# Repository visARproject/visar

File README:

Right now this is just an example of a simple OpenGL program

FIRST

  $ git submodule update --init

BUILDING

  $ scons

RUNNING

  $ build/main

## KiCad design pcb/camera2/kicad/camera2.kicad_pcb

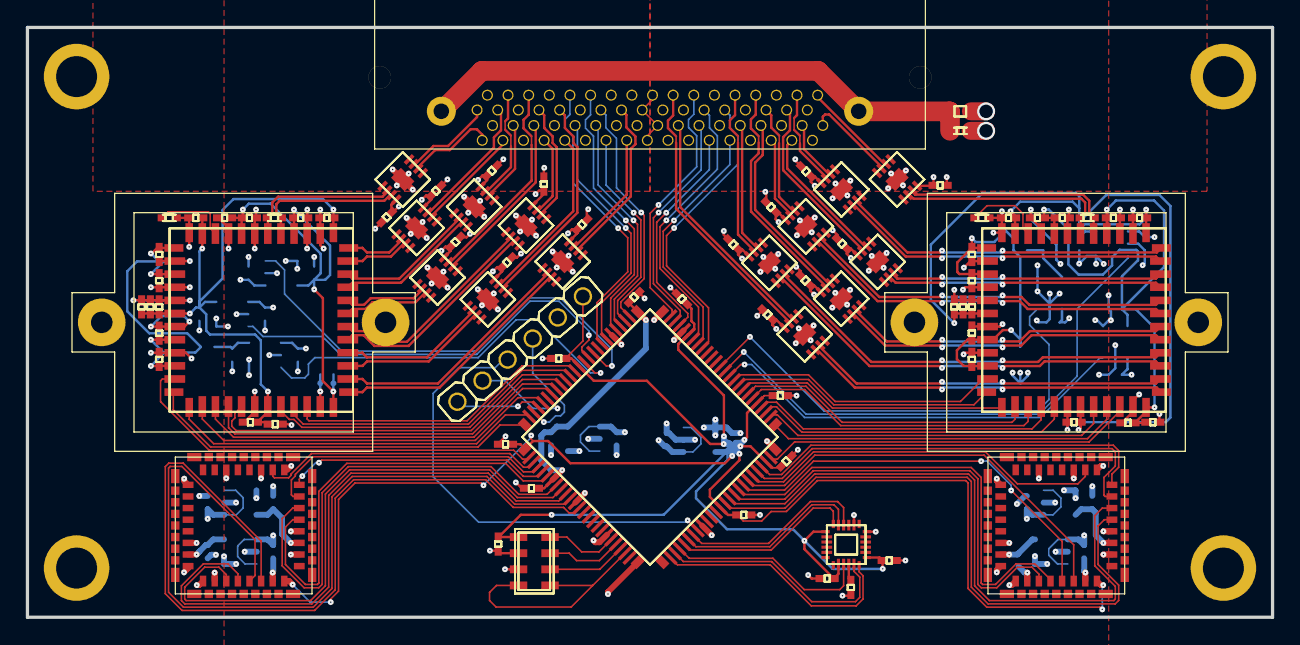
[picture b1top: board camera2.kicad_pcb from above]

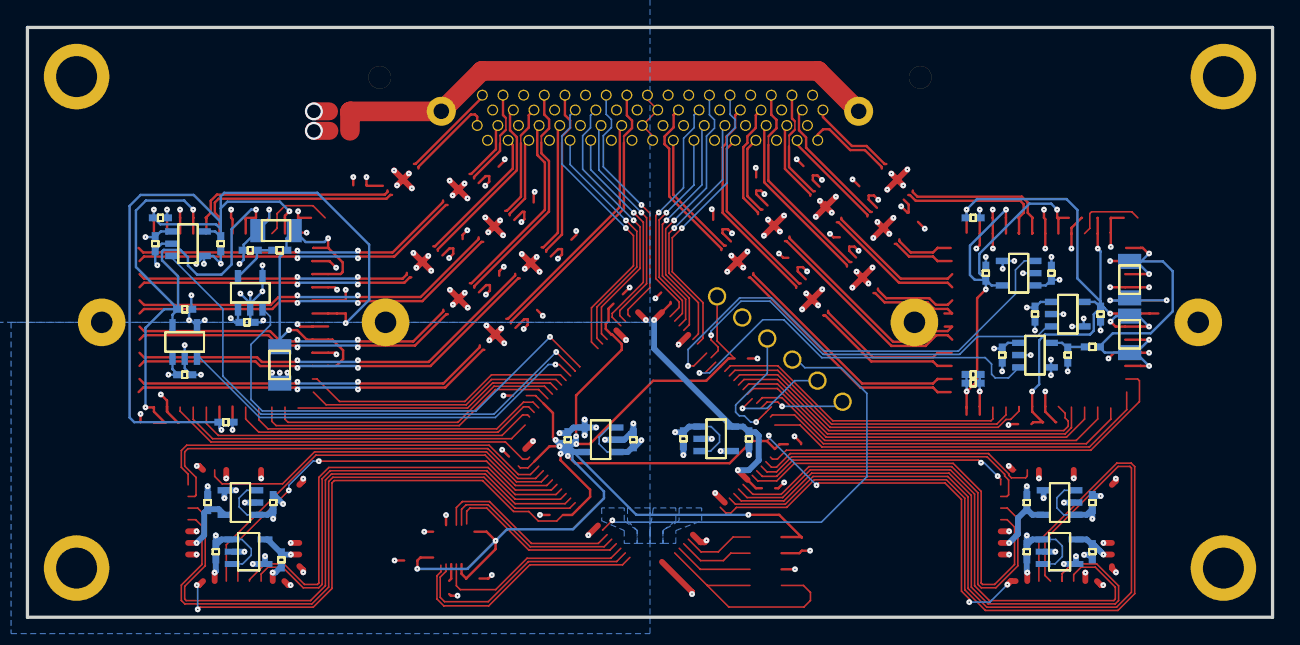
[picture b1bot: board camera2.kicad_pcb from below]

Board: 4 copper layers, 96.5 x 45.7 mm, 137 parts (47 on the bottom side), 147 nets.

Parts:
B1, B2, B3, B4, B5, B6, B10, B11, B15, B16, B17, B18, B19, B20: edc95946fcec597b90e3425252fc97b671c3b31846e543fad6430e1161e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
B1C, B2C, B3C, B4C, B5C, B6C, B10C, B11C, B15C, B16C, B17C, B18C, B19C, B20C: 15aef6ed4df9f5d238c1130cb8f0958fd2b96be76bbd888f3ba8bd3f59a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
C1C10, C1C11, C1C12, C1C20, C1C21, C1C30, C1C31, C1C32, C1C33, C1C40, C1C41, C1C50, C1C51, C1C60, C1C61, C1C62, C1C63, C1_vcc1_8C1, C1_vcc1_8C2, C1_vcc3_0_mainC1, C1_vcc3_0_mainC2, C1_vcc3_0_pixC1, C1_vcc3_0_pixC2, C2C10, C2C11, C2C12, C2C20, C2C21, C2C30, C2C31, C2C32, C2C33, C2C40, C2C41, C2C50, C2C51, C2C60, C2C61, C2C62, C2C63, C2_vcc1_8C1, C2_vcc1_8C2, C2_vcc3_0_mainC1, C2_vcc3_0_mainC2, C2_vcc3_0_pixC1, C2_vcc3_0_pixC2: 15aef6ed4df9f5d238c1130cb8f0958fd2b96be76bbd888f3ba8bd3f59a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
C1C70, C1C71, C2C70, C2C71: 3908cb9356038a1f1fd88f53d6c520b8505039adcfdb7bb53781aaa6f96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
C1FB1, C2FB1: ebac41d1a35a3596bc713c11eee7f61d79ebc7743b0d7c28e1c9b0da10e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
C1M1, C2M1: 468c0146b28c7d95b09a76c88b8cf933647b8d91fd0b27f76627add7a19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
C1R1, C1R2, C2R1, C2R2: 09d18632bfdd592ac9ac4d03ad983c1e61b79906e78d35a2a0c10d4ea12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
C1U1, C2U1: 8f3aa85955296813636e406510ac2cb44b6b28d253d1e3863a516e66fbc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
C1_vcc1_8U, C2_vcc1_8U: f79de117b335608548e97da47262534f56142781502afae22ef8dc1049a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
C1_vcc3_0_mainU, C1_vcc3_0_pixU, C2_vcc3_0_mainU, C2_vcc3_0_pixU: ee49539b4768e16b760bb3db5724cf4fe93de8625e4a25570e978d3eae5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
C2: 8a6750ac66e1a6f76daf3ee494cac9e10424b63c23b0e42452ca9a9228b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
M0, M1, M2, M3: a2599a6c9388b85363dc78da9aac506bd81748babe4024ae1fcc4e84398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
P1: 4d6fcb809a66ef36c471d0496d3ac88d05ca20df7fa16e20f1e1bc387cb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
P2: 1fba3bf286b24dbf25e4bb77a9931907fa57d29a00ed08246cbadd72467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
R2: 09d18632bfdd592ac9ac4d03ad983c1e61b79906e78d35a2a0c10d4ea12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
SC0, SC1, SC2, SC3: 15aef6ed4df9f5d238c1130cb8f0958fd2b96be76bbd888f3ba8bd3f59a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
SU1: 16ea7882d7f656d5472747c5083fa739ddb39b94832403c213f100a5ca7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
SU2: a27f5fc1750a030b9b7e1aa817235c8bcec2c672d71142b492b6f824267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
T1U, T2U: 5a2b29cdda025172b6c1938eb8323d0bef6bb00a32e80d3d8ab82bfb385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
U2: 08c9724177c4578a8ec67f3df913aab08fb61a69285502eb5c729cbf90c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
U2C0, U2C1, U2C2, U2C3, U2C4, U2C5, U2C10, U2C11: 15aef6ed4df9f5d238c1130cb8f0958fd2b96be76bbd888f3ba8bd3f59a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
vcc1_2_1C1, vcc1_2_1C2, vcc1_2_2C1, vcc1_2_2C2, vcc1_8C1, vcc1_8C2, vcc2_8_1C1, vcc2_8_1C2, vcc2_8_2C1, vcc2_8_2C2, vcc3_0C1, vcc3_0C2: 15aef6ed4df9f5d238c1130cb8f0958fd2b96be76bbd888f3ba8bd3f59a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
vcc1_2_1U, vcc1_2_2U: 977feb4d5240b4049db85336d77e98d8d475834df9e877bb1dd515f382d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
vcc1_8U: f79de117b335608548e97da47262534f56142781502afae22ef8dc1049a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
vcc2_8_1U, vcc2_8_2U: 24f375df9bbb308d6324a80bf113e6e8877710000f84949b8ca5fab2c52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
vcc3_0U: ee49539b4768e16b760bb3db5724cf4fe93de8625e4a25570e978d3eae5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

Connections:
C1IBIAS: C1R1.1, C1U1.28
C1MISO: C1U1.3, U2.40
C1MOSI: C1U1.2, U2.41
C1SCLK: C1U1.4, U2.39
C1_ss_n: C1U1.47, U2.42
C1_vcc1_8: C1C10.1, C1C11.1, C1C12.1, C1C20.1, C1C21.1, C1U1.6, C1U1.22, C1U1.26, C1_vcc1_8C2.1, C1_vcc1_8U.5
C1_vcc1_8_en: C1_vcc1_8U.3, U2.35
C1_vcc3_0_main: C1C30.1, C1C31.1, C1C32.1, C1C33.1, C1C40.1, C1C41.1, C1C50.1, C1C51.1, C1U1.1, C1U1.19, C1U1.29, C1U1.36, C1_vcc3_0_mainC2.1, C1_vcc3_0_mainU.5
C1_vcc3_0_main_en: C1_vcc3_0_mainU.3, U2.36
C1_vcc3_0_pix: C1FB1.1, C1_vcc3_0_pixC2.1, C1_vcc3_0_pixU.5
C1_vcc3_0_pix_en: C1_vcc3_0_pixU.3, U2.37
C1monitor0: C1U1.44, U2.46
C1monitor1: C1U1.45, U2.44
C1reset_n: C1U1.46, U2.43
C1trigger0: C1U1.41, U2.52
C1trigger1: C1U1.42, U2.50
C1trigger2: C1U1.43, U2.49
C1vdd_pix: C1C60.1, C1C61.1, C1C62.1, C1C63.1, C1C70.1, C1C71.1, C1FB1.2, C1U1.31, C1U1.33, C1U1.38, C1U1.40
C2IBIAS: C2R1.1, C2U1.28
C2MISO: C2U1.3, U2.1
C2MOSI: C2U1.2, U2.2
C2SCLK: C2U1.4, U2.99
C2_ss_n: C2U1.47, U2.3
C2_vcc1_8: C2C10.1, C2C11.1, C2C12.1, C2C20.1, C2C21.1, C2U1.6, C2U1.22, C2U1.26, C2_vcc1_8C2.1, C2_vcc1_8U.5
C2_vcc1_8_en: C2_vcc1_8U.3, U2.11
C2_vcc3_0_main: C2C30.1, C2C31.1, C2C32.1, C2C33.1, C2C40.1, C2C41.1, C2C50.1, C2C51.1, C2U1.1, C2U1.19, C2U1.29, C2U1.36, C2_vcc3_0_mainC2.1, C2_vcc3_0_mainU.5
C2_vcc3_0_main_en: C2_vcc3_0_mainU.3, U2.12
C2_vcc3_0_pix: C2FB1.1, C2_vcc3_0_pixC2.1, C2_vcc3_0_pixU.5
C2_vcc3_0_pix_en: C2_vcc3_0_pixU.3, U2.13
C2monitor0: C2U1.44, U2.7
C2monitor1: C2U1.45, U2.6
C2reset_n: C2U1.46, U2.4
C2trigger0: C2U1.41, U2.10
C2trigger1: C2U1.42, U2.9
C2trigger2: C2U1.43, U2.8
C2vdd_pix: C2C60.1, C2C61.1, C2C62.1, C2C63.1, C2C70.1, C2C71.1, C2FB1.2, C2U1.31, C2U1.33, C2U1.38, C2U1.40
S_REGOUT: SC1.1, SU2.10
T1MISO: T1U.12, U2.60
T1MOSI: T1U.11, U2.59
T1SCL: T1U.21, U2.56
T1SCLK: T1U.13, U2.61
T1SDA: T1U.22, U2.58
T1_master_clk: T1U.26, U2.53
T1_pwr_dwn_l: T1U.23, U2.54
T1_reset_l: T1U.24, U2.55
T1_ss_n: T1U.14, U2.63
T2MISO: T2U.12, U2.92
T2MOSI: T2U.11, U2.91
T2SCL: T2U.21, U2.89
T2SCLK: T2U.13, U2.93
T2SDA: T2U.22, U2.90
T2_master_clk: T2U.26, U2.95
T2_pwr_dwn_l: T2U.23, U2.96
T2_reset_l: T2U.24, U2.97
T2_ss_n: T2U.14, U2.94
baro_MISO: SU1.6, U2.72
baro_MOSI: SU1.7, U2.71
baro_SCLK: SU1.8, U2.70
baro_spi_nCS: SU1.4, SU1.5, U2.73
cpld_TCK: P2.3, U2.48
cpld_TDI: P2.5, U2.45
cpld_TDO: P2.4, U2.83
cpld_TMS: P2.6, U2.47
gnd: B1.P, B1C.2, B2.P, B2C.2, B3.P, B3C.2, B4.P, B4C.2, B5.P, B5C.2, B6.P, B6C.2, B10.P, B10C.2, B11.P, B11C.2, B15.P, B15C.2, B16.P, B16C.2, B17.P, B17C.2, B18.P, B18C.2, B19.P, B19C.2, B20.P, B20C.2, C1C10.2, C1C11.2, C1C12.2, C1C20.2, C1C21.2, C1C30.2, C1C31.2, C1C32.2, C1C33.2, C1C40.2, C1C41.2, C1C50.2, C1C51.2, C1C60.2, C1C61.2, C1C62.2, C1C63.2, C1C70.2, C1C71.2, C1R1.2, C1U1.5, C1U1.20, C1U1.21, C1U1.25, C1U1.27, C1U1.30, C1U1.32, C1U1.34, C1U1.35, C1U1.37, C1U1.39, C1U1.48, C1_vcc1_8C1.2, C1_vcc1_8C2.2, C1_vcc1_8U.2, C1_vcc1_8U.4, C1_vcc3_0_mainC1.2, C1_vcc3_0_mainC2.2, C1_vcc3_0_mainU.2, C1_vcc3_0_mainU.4, C1_vcc3_0_pixC1.2, C1_vcc3_0_pixC2.2, C1_vcc3_0_pixU.2, C1_vcc3_0_pixU.4, C2.2, C2C10.2, C2C11.2, C2C12.2, C2C20.2, C2C21.2, C2C30.2, C2C31.2, C2C32.2, C2C33.2, C2C40.2, C2C41.2, C2C50.2, C2C51.2, C2C60.2, C2C61.2, C2C62.2, C2C63.2, C2C70.2, C2C71.2, C2R1.2, C2U1.5, C2U1.20, C2U1.21, C2U1.25, C2U1.27, C2U1.30, C2U1.32, C2U1.34, C2U1.35, C2U1.37, C2U1.39, C2U1.48, C2_vcc1_8C1.2, C2_vcc1_8C2.2, C2_vcc1_8U.2, C2_vcc1_8U.4, C2_vcc3_0_mainC1.2, C2_vcc3_0_mainC2.2, C2_vcc3_0_mainU.2, C2_vcc3_0_mainU.4, C2_vcc3_0_pixC1.2, C2_vcc3_0_pixC2.2, C2_vcc3_0_pixU.2, C2_vcc3_0_pixU.4, P1.2, P1.5, P1.8, P1.11, P1.14, P1.21, P1.24, P1.27, P1.30, P1.33, P1.36, P1.39, P1.42, P1.45, P1.48, P1.55, P1.58, P1.61, P1.64, P1.67, P2.2, R2.2, SC0.2, SC1.2, SC2.2, SC3.2, SU1.2, SU1.3, SU2.18, SU2.20, T1U.1, T1U.6, T1U.8, T1U.9, T1U.10, T1U.15, T1U.18, T1U.20, T1U.25, T1U.27, T1U.30, T2U.1, T2U.6, T2U.8, T2U.9, T2U.10, T2U.15, T2U.18, T2U.20, T2U.25, T2U.27, T2U.30, U2.21, U2.25, U2.31, U2.62, U2.69, U2.75, U2.84, U2.100, U2C0.2, U2C1.2, U2C2.2, U2C3.2, U2C4.2, U2C5.2, U2C10.2, U2C11.2, vcc1_2_1C1.2, vcc1_2_1C2.2, vcc1_2_1U.2, vcc1_2_1U.4, vcc1_2_2C1.2, vcc1_2_2C2.2, vcc1_2_2U.2, vcc1_2_2U.4, vcc1_8C1.2, vcc1_8C2.2, vcc1_8U.2, vcc1_8U.4, vcc2_8_1C1.2, vcc2_8_1C2.2, vcc2_8_1U.2, vcc2_8_1U.4, vcc2_8_2C1.2, vcc2_8_2C2.2, vcc2_8_2U.2, vcc2_8_2U.4, vcc3_0C1.2, vcc3_0C2.2, vcc3_0U.2, vcc3_0U.4
imu_FSYNC: SU2.11, U2.78
imu_INT: SU2.12, U2.77
imu_MISO: SU2.9, U2.79
imu_MOSI: SU2.24, U2.80
imu_SCLK: SU2.23, U2.81
imu_spi_nCS: SU2.22, U2.82
out1N: B1.6, C1R2.1, C1U1.24
out1P: B1.7, C1R2.2, C1U1.23
out2N: B2.2, C1U1.18
out2P: B2.3, C1U1.17
out3N: B3.2, C1U1.16
out3P: B3.3, C1U1.15
out4N: B4.2, C1U1.14
out4P: B4.3, C1U1.13
out5N: B5.3, C1U1.11
out5P: B5.2, C1U1.12
out6N: B6.3, C1U1.9
out6P: B6.2, C1U1.10
out10N: B10.3, C1U1.7
out10P: B10.2, C1U1.8
out11N: B11.2, C2U1.7
out11P: B11.3, C2U1.8
out15N: B15.2, C2U1.9
out15P: B15.3, C2U1.10
out16N: B16.2, C2U1.11
out16P: B16.3, C2U1.12
out17N: B17.3, C2U1.14
out17P: B17.2, C2U1.13
out18N: B18.2, C2U1.15
out18P: B18.3, C2U1.16
out19N: B19.2, C2U1.17
out19P: B19.3, C2U1.18
out20N: B20.7, C2R2.2, C2U1.23
out20P: B20.6, C2R2.1, C2U1.24
pair1N: B1.3, P1.35
pair1P: B1.2, P1.1
pair2N: B2.7, P1.37
pair2P: B2.6, P1.3
pair3N: B3.7, P1.38
pair3P: B3.6, P1.4
pair4N: B4.7, P1.40
pair4P: B4.6, P1.6
pair5N: B5.6, P1.41
pair5P: B5.7, P1.7
pair6N: B6.6, P1.43
pair6P: B6.7, P1.9
pair7N: P1.44, U2.33
pair7P: P1.10, U2.32
pair8N: P1.46, U2.30
pair8P: P1.12, U2.29
pair9N: P1.47, U2.27
pair9P: P1.13, U2.28
pair10N: B10.6, P1.49
pair10P: B10.7, P1.15
pair11N: B11.7, P1.54
pair11P: B11.6, P1.20
pair12N: P1.56, U2.24
pair12P: P1.22, U2.23
pair13N: P1.57, U2.19
pair13P: P1.23, U2.22
pair14N: P1.59, U2.17
pair14P: P1.25, U2.18
pair15N: B15.7, P1.60
pair15P: B15.6, P1.26
pair16N: B16.7, P1.62
pair16P: B16.6, P1.28
pair17N: B17.6, P1.63
pair17P: B17.7, P1.29
pair18N: B18.7, P1.65
pair18P: B18.6, P1.31
pair19N: B19.7, P1.66
pair19P: B19.6, P1.32
pair20N: B20.2, P1.68
pair20P: B20.3, P1.34
shield: C2.1, P1.S1, P1.S2, R2.1
vcc1_2_1: T1U.7, vcc1_2_1C2.1, vcc1_2_1U.5
vcc1_2_2: T2U.7, vcc1_2_2C2.1, vcc1_2_2U.5
vcc1_8: U2.26, U2.57, U2C10.1, U2C11.1, vcc1_8C2.1, vcc1_8U.5
vcc2_8_1: T1U.19, vcc2_8_1C2.1, vcc2_8_1U.5
vcc2_8_2: T2U.19, vcc2_8_2C2.1, vcc2_8_2U.5
vcc3_0: P2.1, SC0.1, SC2.1, SC3.1, SU1.1, SU2.1, SU2.8, SU2.13, T1U.16, T2U.16, U2.5, U2.20, U2.38, U2.51, U2.88, U2.98, U2C0.1, U2C1.1, U2C2.1, U2C3.1, U2C4.1, U2C5.1, vcc3_0C2.1, vcc3_0U.5
vcc3_3in: B1.8, B1C.1, B2.8, B2C.1, B3.8, B3C.1, B4.8, B4C.1, B5.8, B5C.1, B6.8, B6C.1, B10.8, B10C.1, B11.8, B11C.1, B15.8, B15C.1, B16.8, B16C.1, B17.8, B17C.1, B18.8, B18C.1, B19.8, B19C.1, B20.8, B20C.1, C1_vcc1_8C1.1, C1_vcc1_8U.1, C1_vcc3_0_mainC1.1, C1_vcc3_0_mainU.1, C1_vcc3_0_pixC1.1, C1_vcc3_0_pixU.1, C2_vcc1_8C1.1, C2_vcc1_8U.1, C2_vcc3_0_mainC1.1, C2_vcc3_0_mainU.1, C2_vcc3_0_pixC1.1, C2_vcc3_0_pixU.1, P1.16, P1.19, P1.50, P1.53, vcc1_2_1C1.1, vcc1_2_1U.1, vcc1_2_1U.3, vcc1_2_2C1.1, vcc1_2_2U.1, vcc1_2_2U.3, vcc1_8C1.1, vcc1_8U.1, vcc1_8U.3, vcc2_8_1C1.1, vcc2_8_1U.1, vcc2_8_1U.3, vcc2_8_2C1.1, vcc2_8_2U.1, vcc2_8_2U.3, vcc3_0C1.1, vcc3_0U.1, vcc3_0U.3
vcc5in: P1.17, P1.18, P1.51, P1.52

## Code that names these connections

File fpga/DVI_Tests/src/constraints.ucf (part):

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NET "right_camera_in_data0_p"  LOC = T12 | IOSTANDARD = LVDS_33 | DIFF_TERM = TRUE;
NET "right_camera_in_data0_n"  LOC = V12 | IOSTANDARD = LVDS_33 | DIFF_TERM = TRUE;

NET "pair7P" LOC = N10 | IOSTANDARD = LVCMOS33;
NET "pair7N" LOC = P11 | IOSTANDARD = LVCMOS33;
NET "pair8P" LOC = M10 | IOSTANDARD = LVCMOS33;
NET "pair8N" LOC = N9  | IOSTANDARD = LVCMOS33;
NET "pair9P" LOC = U11 | IOSTANDARD = LVCMOS33;
NET "pair9N" LOC = V11 | IOSTANDARD = LVCMOS33;

#NET "right_camera_in_clock_p" LOC = R10 | IOSTANDARD = LVDS_33 | DIFF_TERM = TRUE;
#NET "right_camera_in_clock_n" LOC = T10 | IOSTANDARD = LVDS_33 | DIFF_TERM = TRUE;
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#NET "left_camera_in_clock_p" LOC = U10 | IOSTANDARD = LVDS_33 | DIFF_TERM = TRUE;
#NET "left_camera_in_clock_n" LOC = V10 | IOSTANDARD = LVDS_33 | DIFF_TERM = TRUE;

NET "pair12P" LOC = R8 | IOSTANDARD = LVCMOS33;
NET "pair12N" LOC = T8 | IOSTANDARD = LVCMOS33;
NET "pair13P" LOC = M8 | IOSTANDARD = LVCMOS33;
NET "pair13N" LOC = N8 | IOSTANDARD = LVCMOS33;
NET "pair14P" LOC = U8 | IOSTANDARD = LVCMOS33;
NET "pair14N" LOC = V8 | IOSTANDARD = LVCMOS33;

NET "left_camera_in_data0_p"  LOC = U7 | IOSTANDARD = LVDS_33 | DIFF_TERM = TRUE;
NET "left_camera_in_data0_n"  LOC = V7 | IOSTANDARD = LVDS_33 | DIFF_TERM = TRUE;
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
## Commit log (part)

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2015-02-05 delayed start screen renderer
2015-02-07 beacon: add some eclipse directory to gitignore
2015-02-07 beacon: fix potential bug with XBEE TX interrupt when no packets are waiting in queue
2015-02-07 beacon: minor formatting changes
2015-02-08 enable temperature sensor
2015-02-08 initial testing of ALSA audio
2015-02-08 libVisar: Implement working distortion
2015-02-08 Misc: Add .npy and .dat to gitattributes as binary
2015-02-08 Add libVisar python package with rift-specific code
2015-02-08 Add issues section to libvisar redme
2015-02-08 Add build folder to gitignore
2015-02-08 libVisar: Add transformations.py for quaternion->matrix
2015-02-08 Update shaders subpackage
2015-02-08 Create functioning python package
2015-02-09 first good image from camera!
2015-02-09 Add logger utility with variable verbosity levels
2015-02-10 voice control interface instructions
2015-02-10 added distorter_map_decoder_tb.vhd
2015-02-10 fpga: beginning of ethernet support
2015-02-11 progress on comms, mostly untested
2015-02-12 beacon: clean up some xbee.h comments
2015-02-13 cleaned up src repository
2015-02-15 sound updates
2015-02-17 Added xml of menu buttons
2015-02-19 Audio Control Protocol
2015-02-19 audio makefile
2015-02-19 Working Speaker code, untested otherwise
2015-02-21 fpga: removed unused camera files
2015-02-21 fpga: FIFO implementation
2015-02-21 fixed camera_writer limitation
2015-02-21 worked?
2015-02-21 bugfix
2015-02-21 or maybe this is what worked
2015-02-21 writer
2015-02-21 fpga: added util_fifo_fallthrough
2015-02-21 fpga: added and used util_bidir_ram_port_splitter
2015-02-22 fixup! fpga: added and used util_bidir_ram_port_splitter
2015-02-22 work
2015-02-23 reset a debug
2015-02-24 added sleeps for threads with nothing to do
2015-02-24 Add Drawable_List class
2015-02-24 comms changes
2015-02-24 partial update to audio comms
2015-02-26 voice control controller rough draft
2015-03-01 Audio Controller voice controller test code
2015-03-03 audio changes
2015-03-04 python audio controller, tested, bugfixes
2015-03-05 audio/network updates
2015-03-05 network state updates
2015-03-05 networking state updates (actual)
2015-03-05 network testing
2015-03-05 more network testing
2015-03-08 Voice control updated
2015-03-08 Makefile Updated
2015-03-08 Updated Voice Control
2015-03-09 fixed timing errors due to asynchronous reset
2015-03-09 use both cameras
2015-03-09 synthesize ram splitter
2015-03-09 fix some warnings
2015-03-10 use new ram port
2015-03-10 Fixed NULL pointer exception for shutdown sequence
2015-03-10 Added a timer
2015-03-10 sound.c edits
2015-03-10 set pipe to make test
2015-03-10 Verified audio stream
2015-03-10 Added goforward.raw file
2015-03-11 Fixed some define flag stuff but mostly added a read file in for sphinx
2015-03-11 pose handler shell
2015-03-11 fixup to 6f1f34ff0, in which fixing a synthesis warning (below) resulting in incorrect behaviour
    WARNING:Xst:3002 - This design contains one or more registers/latches that are directly
    incompatible with the Spartan6 architecture. The two primary causes of this is
    either a register or latch described with both an asynchronous set and
    asynchronous reset, or a register or latch described with an asynchronous
    set or reset which however has an initialization value of the opposite
    polarity (i.e. asynchronous reset with an initialization value of 1).
2015-03-11 added volume control options
2015-03-11 fpga distortion scripts: changes for new cameras
2015-03-11 corrected bug introduced in fifo synthesis bugfix
2015-03-11 Added more specific debug for voice control
2015-03-11 add 9/10 bit encoder to distorter prefetcher -- decoded still needed in distorter itself
2015-03-11 Fixed input_data.raw output rate
2015-03-11 Added simple dictionary for voice control
2015-03-12 jetson documentation
2015-03-12 Rendering: Add simple unit tests
2015-03-12 Rendering: Fix issue with running as module
2015-03-12 Rendering: Targets rotate to always face camera
2015-03-12 Added example environment as drawable
2015-03-12 Rendering: Add global state tracking sub-module
2015-03-12 Rendering: Make each eye shift by half-IPD along Y axis
2015-03-12 Rendering: Add start of map module
2015-03-12 Rendering: Add requirements list (for Mikey Mike)
2015-03-12 libVisar: Move todo.todo to root folder
2015-03-12 Rendering: Add features to global state tracker
2015-03-12 Rendering: Fix minor bugs in drawables
2015-03-12 Rendering: Add multiple Context drawing to distortion
2015-03-12 Rendering; menu: Add menu button drawable
2015-03-12 Rendering: Move Drawable base class to libVisar.OpenGL
2015-03-12 Rendering: Add todos
2015-03-12 Rendering: Update terrain environment to support new drawable format
2015-03-12 Rendering: Add color to logger
2015-03-12 Rendering: clean up gloo state setting responsibilities
2015-03-12 Rendering: Updates to render_package
2015-03-12 Package OSMViz with libVIsar
2015-03-12 working towards packages
2015-03-12 add pose protocol from etherpad doc in case it goes down again
2015-03-12 Rendering: Fix tabbing in globals
2015-03-15 fpga: do bitslip correctly
2015-03-15 lots of bugfixes
2015-03-15 run second camera
2015-03-15 fpga: retry camera initialization when it fails
2015-03-15 fpga: added resets to FIFO
2015-03-15 display RAM debug info on LEDs
2015-03-15 made ethernet_writer reset properly
2015-03-15 fpga: added extra register in distorter_prefetcher to help timing
2015-03-15 made distorter prefetcher accept RAM starvation by dropping requests instead of corrupting the rest of the frame
2015-03-15 distorter prefetcher: load longer chunks. seems to have fixed artifacts
2015-03-15 fixed some issues that were causing pixels loaded by distorter prefetcher to be out of order
2015-03-15 fixup! display RAM debug info on LEDs
2015-03-15 removed added intelhex debug print
2015-03-15 fpga: add some old edid related files that were hanging around in my working copy
2015-03-15 fpga: add some documentation pdfs that were floating around my working copy
2015-03-16 made bidir_ram_port_splitter reset properly
2015-03-16 updated ram_bandwidth.txt
2015-03-16 added black/grey frame tests to spi_test.py
2015-03-17 force camera data alignment to be closest to sync instead of possibly aligning to different words
2015-03-17 fifo: help timing by registering full/empty signals. adds a cycle of latency from other clock domain ):
2015-03-17 fixed RAM violations in camera_writer - they were due to registering the outputs to the ram, so the write FIFO full flag was effectually observed a cycle earlier than it should have been
2015-03-17 register 10to9 encoding to help timing
2015-03-17 help timing by slowing something down and fixing a register
2015-03-17 Added more robust dictionary
2015-03-19 Rendering: Add demo brain rendering
2015-03-19 Rendering: Add a functional no-distort feature
2015-03-19 Rendering: Minor improvements to drawables
2015-03-22 beacon: port xbee test to actual beacon hardware
2015-03-22 Audio: Add python absolute filepath
2015-03-22 added build script to handle makefile
2015-03-22 Voice Control Handler global state integration
2015-03-22 Pose handler integration
2015-03-22 Semi functional voice parser
2015-03-22 parser integrated into globals
2015-03-22 merged, cleaned up integration
2015-03-22 Fixed bug in parser
2015-03-24 updates to globals
2015-03-24 Added option to call ip addresses directly
2015-03-25 audio handler patch, untested
2015-03-25 add instructions for ad-hoc wifi network from napkin.txt
2015-03-25 network broadcast updated, hardcoded the ad-hoc subnet
2015-03-26 finished testing network.py, removed test outputs
2015-03-26 changed volume command for better arm compatibility
2015-03-26 audio updates, fixed port mismatch
2015-03-26 full audio integration
2015-03-26 audio log update
2015-03-26 error handling for bad user input
2015-03-26 Parser Error handling
2015-03-26 fixed parser bug on one word inputs, vc fully functional with test program
2015-03-28 created do_init in globals, moved action_dict to actions.py
2015-03-29 Changed voice control
2015-03-29 deleted temporary files
2015-03-29 Modified Make and others
2015-03-29 Added delay to voice control
2015-03-29 fix errors with long cables
2015-03-29 SPI WIP
2015-03-29 SCLK thing
2015-03-29 fix start of distorter pipeline being offset
2015-03-29 automatically powering cameras up
2015-03-29 arbiter working
2015-03-29 increased prefetcher command table spacing to avoid occasional visual glitch due to RAM read buffer overrunning
2015-03-29 works
2015-03-29 working?
2015-03-29 edid: come up with new values for 105.6 MHz pixel clock -- needs to be changed in VHDL too
2015-03-30 working pose listener and test code
2015-03-30 patched socket reuse error
2015-03-30 menu fixed, removed logging from vc, seperated from main program
2015-03-30 Updated voice control dictionary
2015-03-31 fireproff init functions
2015-04-02 Made voice control event depentant
2015-04-03 updated jetson documents with further install information
2015-04-03 beacon: 5 Hz update rate
2015-04-03 ros: add beacon_driver -- XXX: implement multipart messages
2015-04-03 fullscreen mode, re-bundled vc program, improved autostart docs
2015-04-04 fifo testbench fix
2015-04-06 WIP device status module
2015-04-09 device controller update
2015-04-09 started integrating device listener, added shutdown command
2015-04-09 Changed menu button colors
2015-04-09 added txros submodule
2015-04-10 fixed fullscreen mode for pyglet backend
2015-04-10 updating autorun instructions
2015-04-15 updated jetson docs, removed outdated information
2015-04-15 beacon ros: improve packet defragmentation -- XXX: needs more test
2015-04-15 controller: add altium files
2015-04-15 pcb: add stencil gerbers as sent to manufacturing
2015-04-15 further integration of controller board
2015-04-16 noticed some errors
2015-04-16 flipped toggle order to reduce error messages
2015-04-16 Visar: Add paths package for getting libvisar directory
2015-04-16 Updated render package
2015-04-16 made pose handler work with beacons
2015-04-16 forced program to use PyGlet backend to fix cashes in QT
2015-04-16 fixed toast font size bug, created text clipping bug
2015-04-17 Documented distortion data loading
2015-04-17 added devices.py to the visar program
2015-04-17 added test for/touch to out.hex to prevent rebuilding
2015-04-17 part 1 startup scripts
2015-04-17 autorun: cleaned up unneeded files, documented
2015-04-17 Add firmware for controller and powerboard
2015-04-18 integrated controller code
2015-04-18 udev rules for visar
2015-04-18 Functional battery icon
2015-04-18 shutdown signal from powerboard
2015-04-18 beacon firmware: enable subframe message output
2015-04-18 power board integration
2015-04-18 setup udev rules for power, controller, Xbee
2015-04-18 add beacon_xbee test script
2015-04-18 Debug for voice control started
2015-04-18 added driver module for FPGA
2015-04-18 updated rules, fixed typos
2015-04-19 beacon_xbee: change serial port name to match visAR udev rule because josh can't use git ;)
2015-04-19 documented bugfix
2015-04-19 rules update and reset signa
2015-04-19 audio bugfixes; prevent self calls, shutdown while call active is fixed
2015-04-19 Revert "new camera calibration"
    This reverts commit 8c1e23e4c4619d500fa45def54663535855b6dec.
2015-04-19 fpga uart reset support
2015-04-19 visar_gps: launch file changes
2015-04-19 WIP GPS integration
2015-04-20 try-catch block for audio socket bind error
2015-04-20 vsr hold timer
2015-04-20 added hold timer to start->stop vc commands
2015-04-20 fixed audio pipe not being deleted
2015-04-20 no audio mode
2015-04-20 moved battery icon
2015-04-20 Changed Pose server port to match ROS node
2015-04-20 device fixes
2015-04-20 test hack
2015-04-20 modified menu buttons
2015-04-20 fixed calltarget
2015-04-20 autorun.sh
2015-04-21 moved the battery over
2015-04-21 moved the battery icon
2015-04-23 beacon ros: copy parser script from skytraq_driver
2015-04-24 moved speaker thread to realtime priority
2015-05-01 cleaned up status comments in c files
2015-05-04 vsr program support for external audio program
2015-05-05 Manually controlling when speaker thread blocks, grouped write operations
2015-05-29 reverted debug changes
